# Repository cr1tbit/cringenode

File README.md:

# MOSNode

### A hackable IoT load switch prototyping platform

This device was probably the peak of my overengineeringness - I decided to create the most universal board for controlling low voltage outputs (Like LED stripes, motors, etc.).

In the end, it was too annoying to setup the matrix connections, so I just abandoned it.

## License

Copyright 2023 Jakub "cr1tbit" Sadowski.

* **Hardware** (KiCad sources, production files and this documentation) is
  licensed under the [CERN-OHL-P v2](LICENSE) (permissive). You may
  redistribute and modify it and make products using it under the terms of
  that licence.
* **Firmware** in [MOSNode-fw/](outduino-fw/) is licensed under the
  [MIT License](outduino-fw/LICENSE).

This source is distributed WITHOUT ANY EXPRESS OR IMPLIED WARRANTY, INCLUDING
OF MERCHANTABILITY, SATISFACTORY QUALITY AND FITNESS FOR A PARTICULAR PURPOSE.
Please see the CERN-OHL-P v2 for applicable conditions.

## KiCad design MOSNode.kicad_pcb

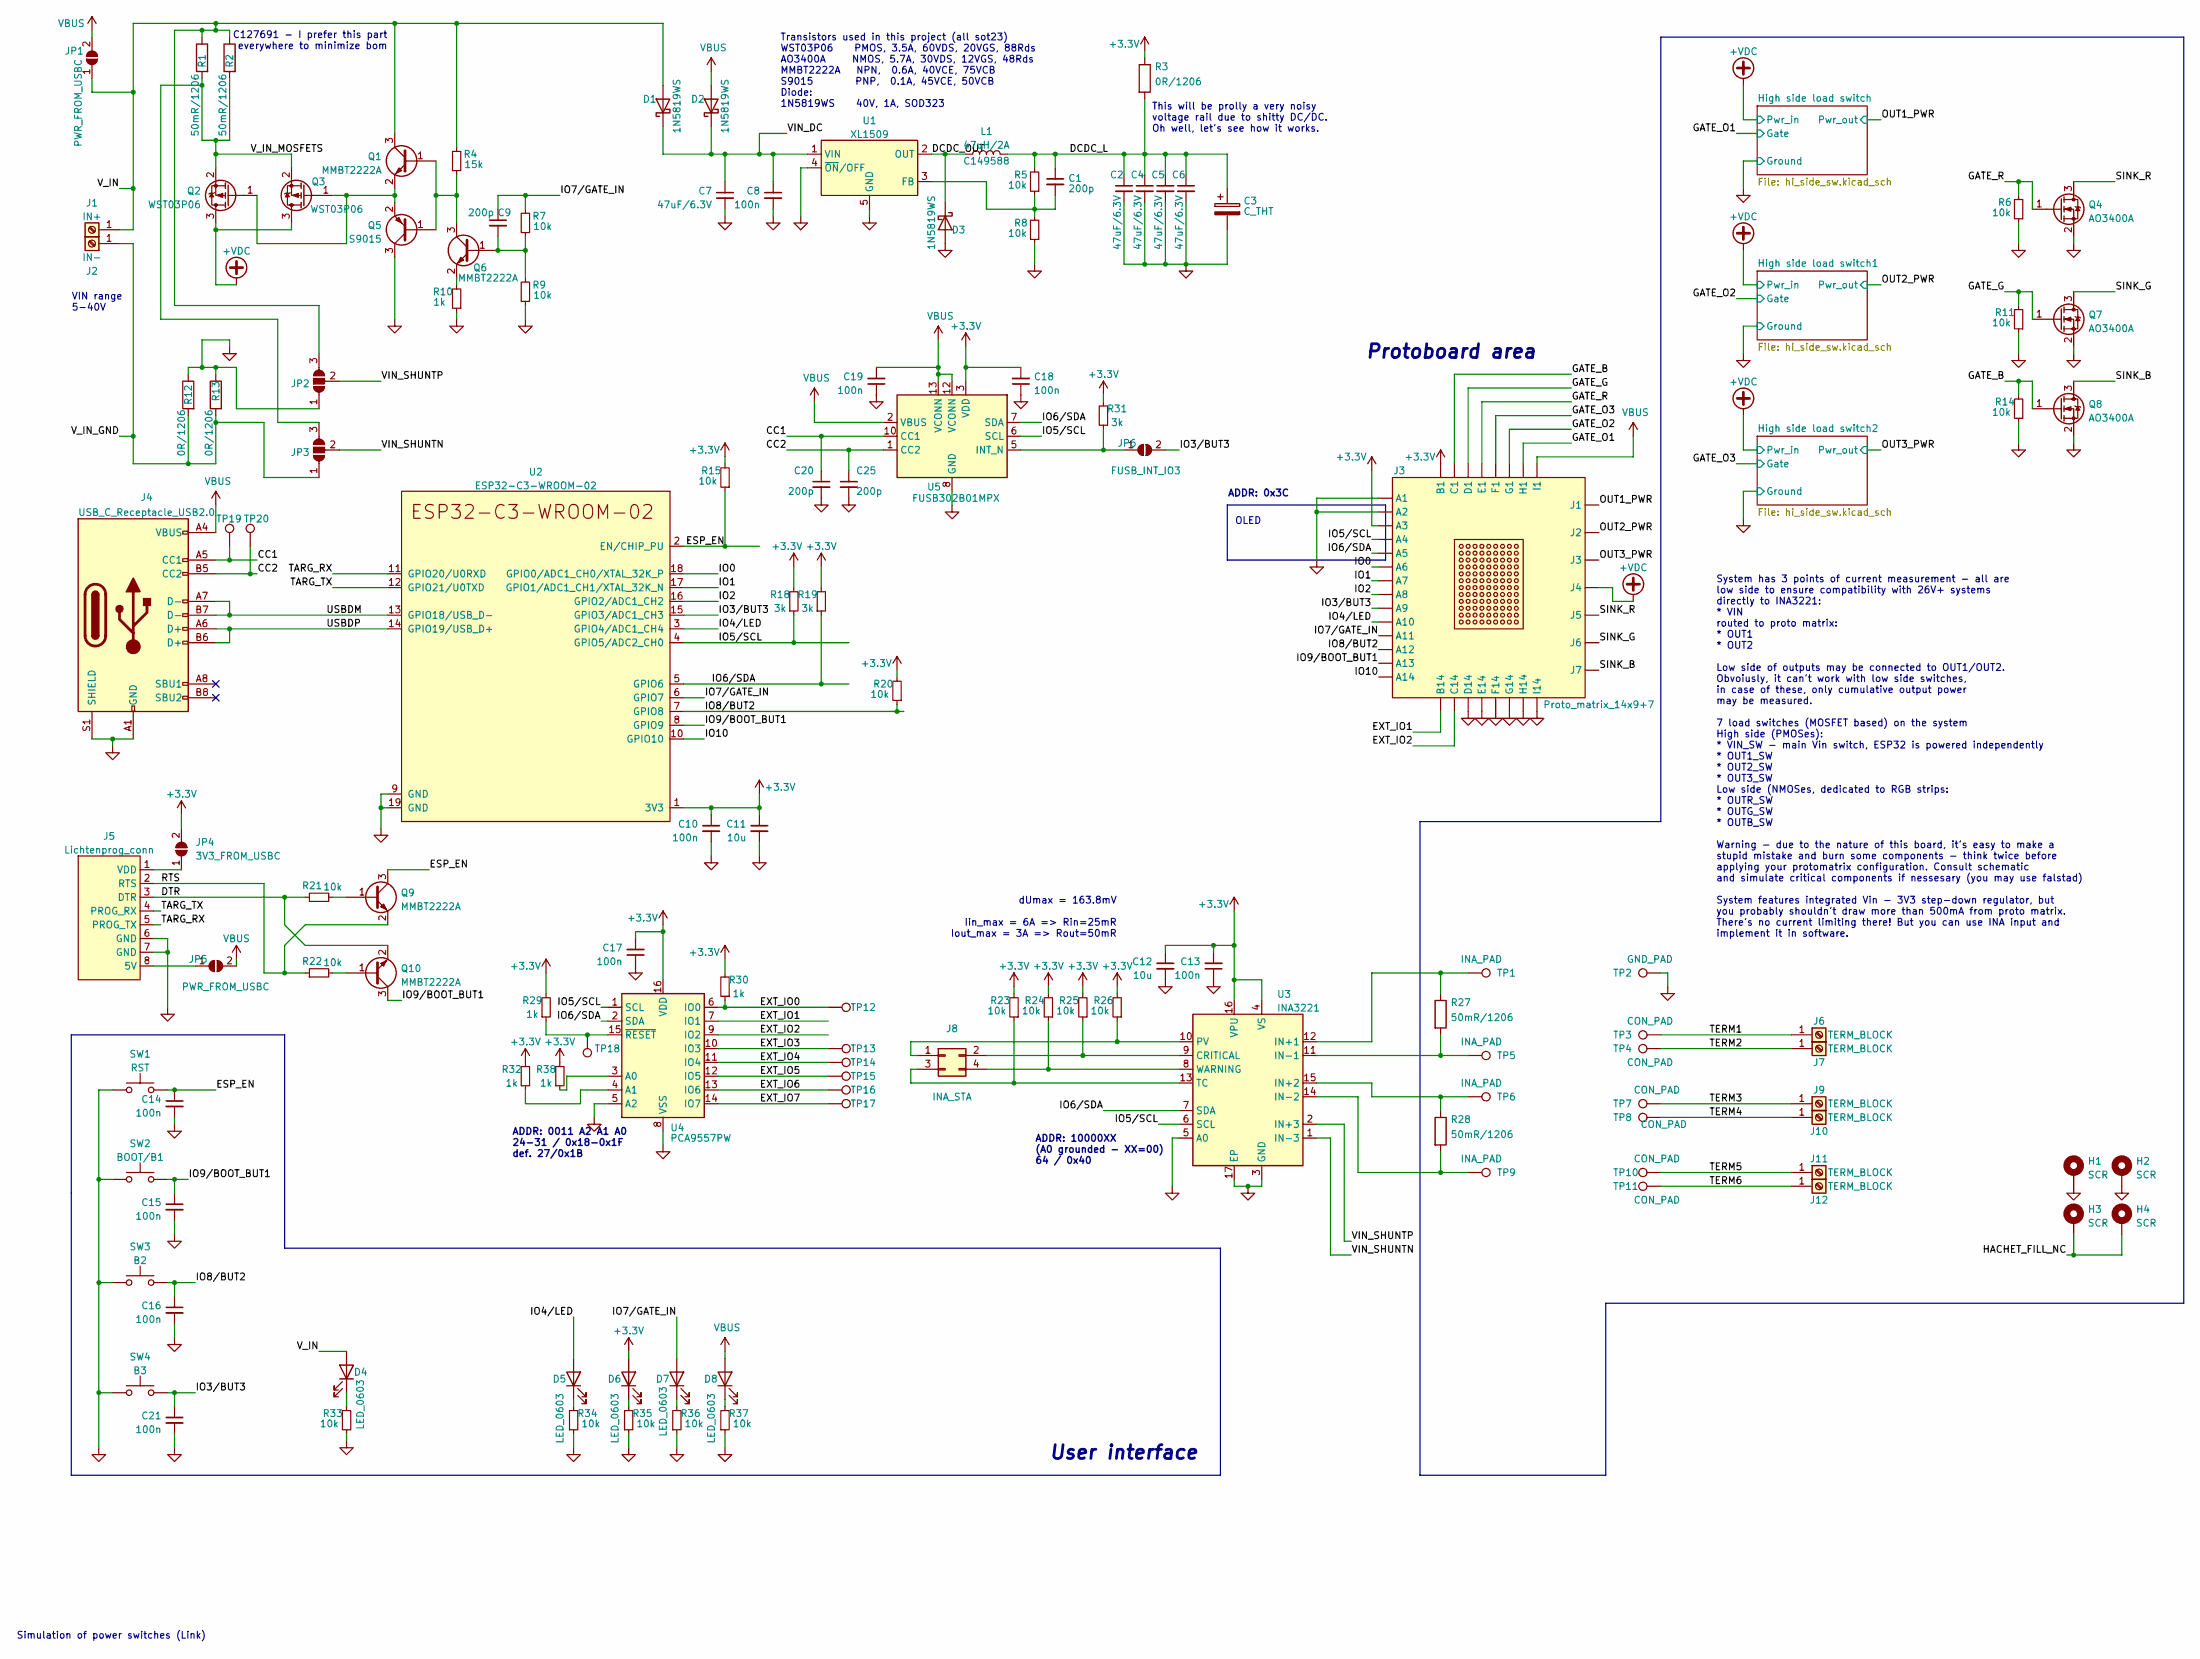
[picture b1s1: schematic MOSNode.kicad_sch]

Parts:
C1, C9, C20, C25: 200p; C_0402_1005Metric; LCSC C1530
C2, C4, C5, C6, C7: 47uF/6.3V; C_1206_3216Metric; LCSC C96123
C3: C_THT; CP_Radial_D10.0mm_P7.50mm; LCSC DNP
C8, C10, C13, C14, C15, C16, C17, C18, C19, C21: 100n; C_0402_1005Metric; LCSC C307331
C11, C12: 10u; C_0402_1005Metric; LCSC C15525
D1, D2, D3: 1N5819WS; D_SOD-323; LCSC C191023
D4, D5, D6, D7, D8: LED_0603; LED_0603_1608Metric_Pad1.05x0.95mm_HandSolder; LCSC C2290
H1, H2, H3, H4: SCR; MountingHole_3.2mm_M3_Pad_TopOnly; LCSC DNP
J1: IN+; DG235-5.0; LCSC DNP
J2: IN-; DG235-5.0; LCSC DNP
J3: Proto_matrix_14x9+7; LCSC DNP
J4: USB_C_Receptacle_USB2.0; USB_C_Receptacle_HRO_TYPE-C-31-M-12; LCSC C165948
J5: Lichtenprog_conn; Lichtenprog; LCSC DNP
J6, J7, J9, J10, J11, J12: TERM_BLOCK; DG235-5.0; LCSC DNP
J8: INA_STA; PinHeader_2x02_P2.54mm_Vertical; LCSC DNP
JP1, JP5: PWR_FROM_USBC; SolderJumper-2_P1.3mm_Open_TrianglePad1.0x1.5mm; LCSC DNP
JP2, JP3: SolderJumper_3_Open; SolderJumper-3_P2.0mm_Open_TrianglePad1.0x1.5mm_NumberLabels; LCSC DNP
JP4: 3V3_FROM_USBC; SolderJumper-2_P1.3mm_Open_TrianglePad1.0x1.5mm; LCSC DNP
JP6: FUSB_INT_IO3; SolderJumper-2_P1.3mm_Open_TrianglePad1.0x1.5mm; LCSC DNP
L1: 47uH/2A; L_Abracon_ASPI-0630LR; JLC C149588
Q1, Q6, Q9, Q10: MMBT2222A; SOT-23; LCSC C8512
Q2, Q3: WST03P06; SOT-23; LCSC C105166
Q4, Q7, Q8: AO3400A; SOT-23; LCSC C20917
Q5: S9015; SOT-23; LCSC C2149
R1, R2, R27, R28: 50mR/1206; R_1206_3216Metric_Pad1.30x1.75mm_HandSolder; LCSC C601102
R3, R12, R13: 0R/1206; R_1206_3216Metric_Pad1.30x1.75mm_HandSolder; LCSC C17888
R4: 15k; R_0402_1005Metric; LCSC C25756
R5, R6, R7, R8, R9, R11, R14, R15, R20, R21, R22, R23, R24, R25, R26, R33, R34, R35, R36, R37: 10k; R_0402_1005Metric; LCSC C25744
R10, R29, R30, R32, R38: 1k; R_0402_1005Metric; LCSC C11702
R18, R19, R31: 3k; R_0402_1005Metric; LCSC C25890
SW1: RST; SW_SPST_FSMSM; LCSC DNP
SW2: BOOT/B1; SW_SPST_FSMSM; LCSC DNP
SW3: B2; SW_SPST_FSMSM; LCSC DNP
SW4: B3; SW_SPST_FSMSM; LCSC DNP
TP1, TP5, TP6, TP9: INA_PAD; TestPoint_Pad_D2.5mm; LCSC DNP
TP2: GND_PAD; TestPoint_Pad_D2.5mm; LCSC DNP
TP3, TP4, TP7, TP8, TP10, TP11: CON_PAD; MountingHole_2.7mm_M2.5_DIN965_Pad; LCSC DNP
TP12, TP13, TP14, TP15, TP16, TP17, TP18, TP19, TP20: IOPAD; TestPoint_Pad_D1.0mm; LCSC DNP
U1: XL1509; SOIC-8_3.9x4.9mm_P1.27mm; LCSC C74192
U2: ESP32-C3-WROOM-02; LCSC DNP
U3: INA3221; Texas_RGV_S-PVQFN-N16_EP2.1x2.1mm; LCSC DNP
U4: PCA9557PW; TSSOP-16_4.4x5mm_P0.65mm; LCSC C141380
U5: FUSB302B01MPX; WQFN-14-1EP_2.5x2.5mm_P0.5mm_EP1.45x1.45mm; LCSC C132291

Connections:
+3.3V: C10.1, C11.1, C12.1, C13.2, C17.2, C18.2, D6.2 (A), J3.A3, J3.B1, JP4.2 (B), R3.1, R15.2, R18.2, R19.2, R20.2, R23.2, R24.2, R25.2, R26.2, R29.2, R30.2, R31.2, R32.2, R38.2, U2.1 (3V3), U3.4 (VS), U3.16 (VPU), U4.16 (VDD), U5.3 (VDD), U5.4 (VDD)
+VDC: J3.J4, Q2.3 (S), Q3.3 (S); also elsewhere on the board
/CC1: C20.1, J4.A5 (CC1), TP19.1, U5.10 (CC1), U5.11 (CC1)
/CC2: C25.1, J4.B5 (CC2), TP20.1, U5.1 (CC2), U5.14 (CC2)
/DCDC_L: C1.1, C2.1, C3.1, C4.1, C5.1, C6.1, L1.2, R3.2, R5.2
/DCDC_OUT: D3.1 (K), L1.1, U1.2 (OUT)
/DTR: J5.3 (DTR), Q10.2 (E), R21.1
/ESP_EN: C14.1, Q9.3 (C), R15.1, SW1.2, U2.2 (EN/CHIP_PU)
/EXT_IO0: R30.1, TP12.1, U4.6 (IO0)
/EXT_IO1: J3.B14, U4.7 (IO1)
/EXT_IO2: J3.C14, U4.9 (IO2)
/EXT_IO3: TP13.1, U4.10 (IO3)
/EXT_IO4: TP14.1, U4.11 (IO4)
/EXT_IO5: TP15.1, U4.12 (IO5)
/EXT_IO6: TP16.1, U4.13 (IO6)
/EXT_IO7: TP17.1, U4.14 (IO7)
/GATE_B: J3.C1, Q8.1 (G), R14.2
/GATE_G: J3.D1, Q7.1 (G), R11.2
/GATE_O1: J3.H1; also elsewhere on the board
/GATE_O2: J3.G1; also elsewhere on the board
/GATE_O3: J3.F1; also elsewhere on the board
/GATE_R: J3.E1, Q4.1 (G), R6.2
/HACHET_FILL_NC: H3.1, H4.1
/IO0: J3.A6, U2.18 (GPIO0/ADC1_CH0/XTAL_32K_P)
/IO1: J3.A7, U2.17 (GPIO1/ADC1_CH1/XTAL_32K_N)
/IO2: J3.A8, U2.16 (GPIO2/ADC1_CH2)
/IO3/BUT3: C21.1, J3.A9, JP6.2 (B), SW4.2, U2.15 (GPIO3/ADC1_CH3)
/IO4/LED: D5.2 (A), J3.A10, U2.3 (GPIO4/ADC1_CH4)
/IO5/SCL: J3.A4, R18.1, U2.4 (GPIO5/ADC2_CH0), U3.6 (SCL), U4.1 (SCL), U5.6 (SCL)
/IO6/SDA: J3.A5, R19.1, U2.5 (GPIO6), U3.7 (SDA), U4.2 (SDA), U5.7 (SDA)
/IO7/GATE_IN: C9.1, D7.2 (A), J3.A11, R7.2, U2.6 (GPIO7)
/IO8/BUT2: C16.1, J3.A12, R20.1, SW3.2, U2.7 (GPIO8)
/IO9/BOOT_BUT1: C15.1, J3.A13, Q10.3 (C), SW2.2, U2.8 (GPIO9)
/IO10: J3.A14, U2.10 (GPIO10)
/OUT1_PWR: J3.J1; also elsewhere on the board
/OUT2_PWR: J3.J2; also elsewhere on the board
/OUT3_PWR: J3.J3; also elsewhere on the board
/RTS: J5.2 (RTS), Q9.2 (E), R22.1
/SINK_B: J3.J7, Q8.3 (D)
/SINK_G: J3.J6, Q7.3 (D)
/SINK_R: J3.J5, Q4.3 (D)
/TARG_RX: J5.5 (PROG_TX), U2.11 (GPIO20/U0RXD)
/TARG_TX: J5.4 (PROG_RX), U2.12 (GPIO21/U0TXD)
/TERM1: J6.1, TP3.1
/TERM2: J7.1, TP4.1
/TERM3: J9.1, TP7.1
/TERM4: J10.1, TP8.1
/TERM5: J11.1, TP10.1
/TERM6: J12.1, TP11.1
/USBDM: J4.A7 (D-), J4.B7 (D-), U2.13 (GPIO18/USB_D-)
/USBDP: J4.A6 (D+), J4.B6 (D+), U2.14 (GPIO19/USB_D+)
/VIN_DC: C7.1, C8.1, D1.1 (K), D2.1 (K), U1.1 (VIN)
/VIN_SHUNTN: JP3.2 (C), U3.1 (IN-3)
/VIN_SHUNTP: JP2.2 (C), U3.2 (IN+3)
/V_IN: D1.2 (A), D4.2 (A), J1.1, JP1.1 (A), JP2.3 (B), Q1.3 (C), R1.1, R2.1, R4.2
/V_IN_GND: J2.1, JP3.1 (A), R12.2, R13.2
/V_IN_MOSFETS: JP3.3 (B), Q2.2 (D), Q3.2 (D), R1.2, R2.2
GND: C2.2, C3.2, C4.2, C5.2, C6.2, C7.2, C8.2, C10.2, C11.2, C12.2, C13.1, C14.2, C15.2, C16.2, C17.1, C18.1, C19.1, C20.2, C21.2, C25.2, D3.2 (A), H1.1, H2.1, J3.A1, J3.A2, J3.D14, J3.E14, J3.F14, J3.G14, J3.H14, J3.I14, J4.A1 (GND), J4.A12 (GND), J4.B1 (GND), J4.B12 (GND), J4.S1 (SHIELD), J5.6 (GND), J5.7 (GND), JP2.1 (A), Q4.2 (S), Q5.3 (C), Q7.2 (S), Q8.2 (S), R6.1, R8.1, R9.1, R10.1, R11.1, R12.1, R13.1, R14.1, R33.1, R34.1, R35.1, R36.1, R37.1, SW1.1, SW2.1, SW3.1, SW4.1, TP2.1, U1.4 (~ON/OFF), U1.5 (GND), U1.6 (GND), U1.7 (GND), U1.8 (GND), U2.9 (GND), U2.19 (GND), U3.3 (GND), U3.5 (A0), U3.17 (EP), U4.5 (A2), U4.8 (VSS), U5.8 (GND), U5.9 (GND), U5.15 (GND); also elsewhere on the board
unnamed: D4.1 (K), R33.2
unnamed: D5.1 (K), R34.2
unnamed: D6.1 (K), R35.2
unnamed: D7.1 (K), R36.2
unnamed: D8.1 (K), R37.2
unnamed: J5.8 (5V), JP5.1 (A)
unnamed: J5.1 (VDD), JP4.1 (A)
unnamed: J8.1, R26.1, U3.10 (PV)
unnamed: J8.2, R25.1, U3.9 (CRITICAL)
unnamed: J8.3, R23.1, U3.13 (TC)
unnamed: J8.4, R24.1, U3.8 (WARNING)
unnamed: JP6.1 (A), R31.1, U5.5 (INT_N)
unnamed: Q1.1 (B), Q5.1 (B), Q6.3 (C), R4.1
unnamed: Q1.2 (E), Q2.1 (G), Q3.1 (G), Q5.2 (E)
unnamed: C9.2, Q6.1 (B), R7.1, R9.2
unnamed: Q6.2 (E), R10.2
unnamed: Q9.1 (B), R21.2
unnamed: Q10.1 (B), R22.2
unnamed: C1.2, R5.1, R8.2, U1.3 (FB)
unnamed: R27.1, TP1.1, U3.12 (IN+1)
unnamed: R28.1, TP6.1, U3.15 (IN+2)
unnamed: R27.2, TP5.1, U3.11 (IN-1)
unnamed: R28.2, TP9.1, U3.14 (IN-2)
unnamed: R38.1, U4.3 (A0)
unnamed: R32.1, U4.4 (A1)
unnamed: R29.1, TP18.1, U4.15 (~RESET)
VBUS: C19.2, D2.2 (A), D8.2 (A), J3.I1, J4.A4 (VBUS), J4.A9 (VBUS), J4.B4 (VBUS), J4.B9 (VBUS), JP1.2 (B), JP5.2 (B), U5.2 (VBUS), U5.12 (VCONN), U5.13 (VCONN)

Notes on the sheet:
ADDR: 0011 A2 A1 A0 24-31 / 0x18-0x1F def. 27/0x1B
Transistors used in this project (all sot23) WST03P06 PMOS, 3.5A, 60VDS, 20VGS, 88Rds AO3400A NMOS, 5.7A, 30VDS, 12VGS, 48Rds MMBT2222A NPN, 0.6A, 40VCE, 75VCB S9015 PNP, 0.1A, 45VCE, 50VCB Diode: 1N5819WS 40V, 1A, SOD323
Protoboard area
ADDR: 10000XX (A0 grounded - XX=00) 64 / 0x40
System has 3 points of current measurement - all are low side to ensure compatibility with 26V+ systems directly to INA3221: * VIN routed to proto matrix: * OUT1 * OUT2 Low side of outputs may be connected to OUT1/OUT2. Obvoiusly, it can't work with low side switches, in case of these, only cumulat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
VIN range 5-40V
This will be prolly a very noisy voltage rail due to shitty DC/DC. Oh well, let's see how it works.
OLED
ADDR: 0x3C
User interface
C127691 - I prefer this part everywhere to minimize bom
Simulation of power switches (Link)
dUmax = 163.8mV Iin_max = 6A => Rin=25mR Iout_max = 3A => Rout=50mR

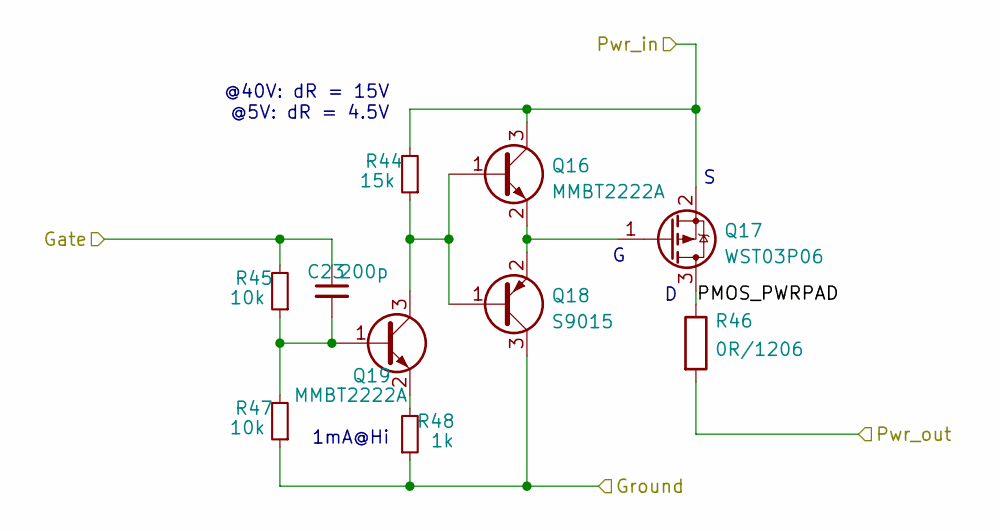
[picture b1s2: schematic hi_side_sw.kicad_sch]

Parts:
C23: 200p; C_0402_1005Metric; LCSC C1530
Q16, Q19: MMBT2222A; SOT-23; LCSC C8512
Q17: WST03P06; SOT-23; LCSC C105166
Q18: S9015; SOT-23; LCSC C2149
R44: 15k; R_0402_1005Metric; LCSC C25756
R45, R47: 10k; R_0402_1005Metric; LCSC C25744
R46: 0R/1206; R_1206_3216Metric_Pad1.30x1.75mm_HandSolder; LCSC C17888
R48: 1k; R_0402_1005Metric; LCSC C11702

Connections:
+VDC: Q16.3 (C), Q17.2 (D), R44.2; also elsewhere on the board
/GATE_O1: C23.1, R45.2; also elsewhere on the board
/High side load switch/PMOS_PWRPAD: Q17.3 (S), R46.1
/OUT1_PWR: R46.2; also elsewhere on the board
GND: Q18.3 (C), R47.1, R48.1; also elsewhere on the board
unnamed: Q16.1 (B), Q18.1 (B), Q19.3 (C), R44.1
unnamed: Q16.2 (E), Q17.1 (G), Q18.2 (E)
unnamed: C23.2, Q19.1 (B), R45.1, R47.2
unnamed: Q19.2 (E), R48.2

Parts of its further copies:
C22, C24: 200p; C_0402_1005Metric; LCSC C1530
Q12, Q15, Q20, Q23: MMBT2222A; SOT-23; LCSC C8512
Q13, Q21: WST03P06; SOT-23; LCSC C105166
Q14, Q22: S9015; SOT-23; LCSC C2149
R39, R49: 15k; R_0402_1005Metric; LCSC C25756
R40, R42, R50, R52: 10k; R_0402_1005Metric; LCSC C25744
R41, R51: 0R/1206; R_1206_3216Metric_Pad1.30x1.75mm_HandSolder; LCSC C17888
R43, R53: 1k; R_0402_1005Metric; LCSC C11702

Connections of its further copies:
+VDC: Q12.3 (C), Q13.2 (D), Q20.3 (C), Q21.2 (D), R39.2, R49.2; also elsewhere on the board
/GATE_O2: C22.1, R40.2; also elsewhere on the board
/GATE_O3: C24.1, R50.2; also elsewhere on the board
/High side load switch1/PMOS_PWRPAD: Q13.3 (S), R41.1
/High side load switch2/PMOS_PWRPAD: Q21.3 (S), R51.1
/OUT2_PWR: R41.2; also elsewhere on the board
/OUT3_PWR: R51.2; also elsewhere on the board
GND: Q14.3 (C), Q22.3 (C), R42.1, R43.1, R52.1, R53.1; also elsewhere on the board
unnamed: Q12.1 (B), Q14.1 (B), Q15.3 (C), R39.1
unnamed: Q12.2 (E), Q13.1 (G), Q14.2 (E)
unnamed: C22.2, Q15.1 (B), R40.1, R42.2
unnamed: Q15.2 (E), R43.2
unnamed: Q20.1 (B), Q22.1 (B), Q23.3 (C), R49.1
unnamed: Q20.2 (E), Q21.1 (G), Q22.2 (E)
unnamed: C24.2, Q23.1 (B), R50.1, R52.2
unnamed: Q23.2 (E), R53.2

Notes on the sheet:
1mA@Hi
@40V: dR = 15V @5V: dR = 4.5V

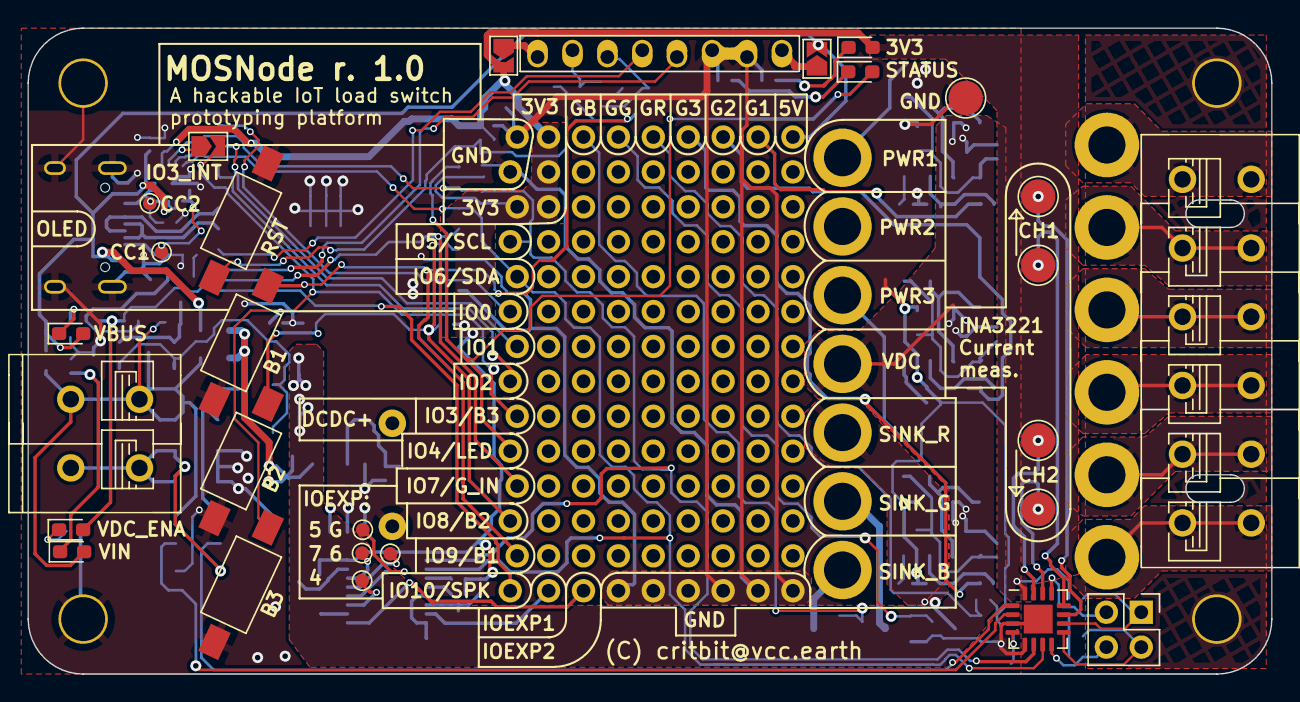
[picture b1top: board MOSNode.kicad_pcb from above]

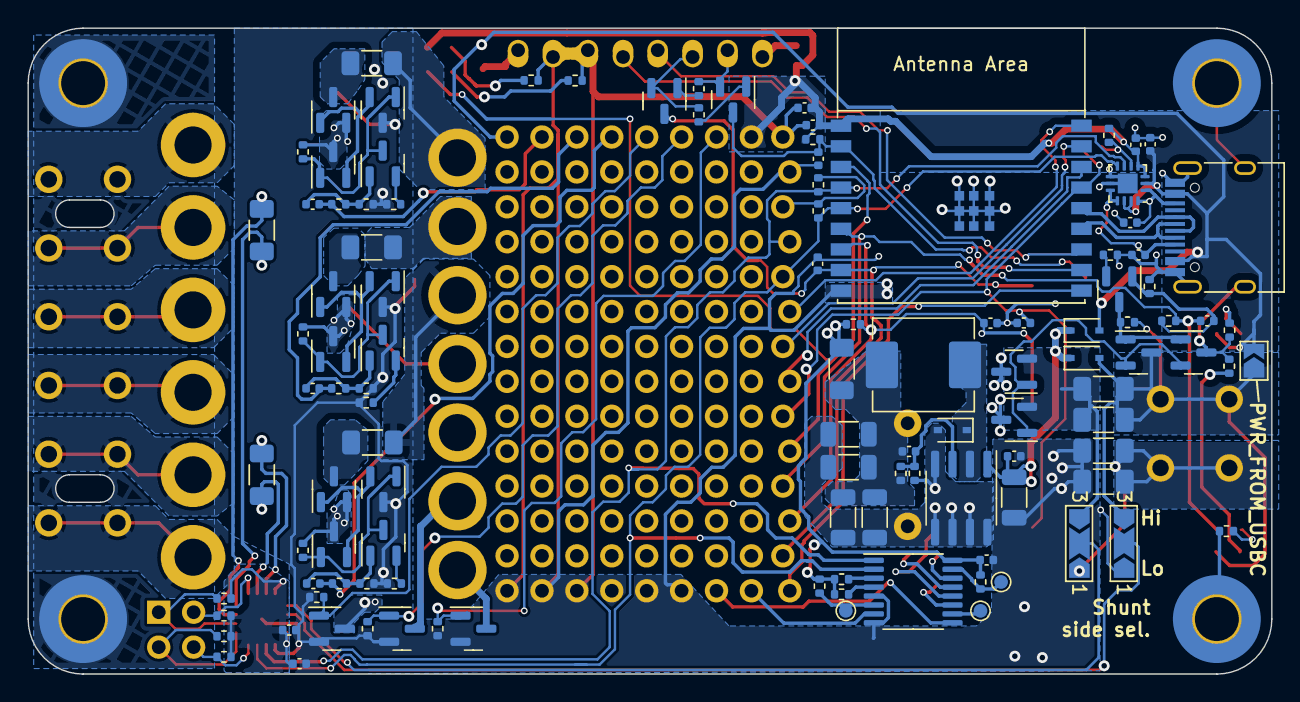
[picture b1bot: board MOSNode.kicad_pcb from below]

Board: 2 copper layers, 90.5 x 47.0 mm, 158 parts (116 on the bottom side), 100 nets.

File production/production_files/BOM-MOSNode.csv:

Comment,Designator,Footprint,LCSC
WST03P06,"Q13,Q17,Q2,Q21,Q3",SOT-23,C105166
1k,"R10,R29,R30,R32,R38,R43,R48,R53",R_0402_1005Metric,C11702
FUSB302B01MPX,U5,WQFN-14-1EP_2.5x2.5mm_P0.5mm_EP1.45x1.45mm,C132291
PCA9557PW,U4,TSSOP-16_4.4x5mm_P0.65mm,C141380
47uH/2A,L1,L_Abracon_ASPI-0630LR,C149588
200p,"C1,C20,C22,C23,C24,C25,C9",C_0402_1005Metric,C1530
10u,"C11,C12",C_0402_1005Metric,C15525
USB_C_Receptacle_USB2.0,J4,USB_C_Receptacle_HRO_TYPE-C-31-M-12,C165948
0R/1206,"R12,R13,R3,R41,R46,R51",R_1206_3216Metric_Pad1.30x1.75mm_HandSolder,C17888
1N5819WS,"D1,D2,D3",D_SOD-323,C191023
AO3400A,"Q4,Q7,Q8",SOT-23,C20917
S9015,"Q14,Q18,Q22,Q5",SOT-23,C2149
LED_0603,"D4,D5,D6,D7,D8",LED_0603_1608Metric_Pad1.05x0.95mm_HandSolder,C2290
10k,"R11,R14,R15,R20,R21,R22,R23,R24,R25,R26,R33,R34,R35,R36,R37,R40,R42,R45,R47,R5,R50,R52,R6,R7,R8,R9",R_0402_1005Metric,C25744
15k,"R39,R4,R44,R49",R_0402_1005Metric,C25756
3k,"R18,R19,R31",R_0402_1005Metric,C25890
100n,"C10,C13,C14,C15,C16,C17,C18,C19,C21,C8",C_0402_1005Metric,C307331
50mR/1206,"R1,R2,R27,R28",R_1206_3216Metric_Pad1.30x1.75mm_HandSolder,C601102
XL1509,U1,SOIC-8_3.9x4.9mm_P1.27mm,C74192
MMBT2222A,"Q1,Q10,Q12,Q15,Q16,Q19,Q20,Q23,Q6,Q9",SOT-23,C8512
47uF/6.3V,"C2,C4,C5,C6,C7",C_1206_3216Metric,C96123
IN+,J1,DG235-5.0,
FUSB_INT_IO3,JP6,SolderJumper-2_P1.3mm_Open_TrianglePad1.0x1.5mm,
INA_PAD,TP5,TestPoint_Pad_D2.5mm,
B3,SW4,SW_SPST_FSMSM,
TERM_BLOCK,J7,DG235-5.0,
CON_PAD,TP4,MountingHole_2.7mm_M2.5_DIN965_Pad,
INA_STA,J8,PinHeader_2x02_P2.54mm_Vertical,
CON_PAD,TP11,MountingHole_2.7mm_M2.5_DIN965_Pad,
INA_PAD,TP9,TestPoint_Pad_D2.5mm,
BOOT/B1,SW2,SW_SPST_FSMSM,
TERM_BLOCK,J10,DG235-5.0,
TERM_BLOCK,J6,DG235-5.0,
INA_PAD,TP1,TestPoint_Pad_D2.5mm,
IOPAD,TP20,TestPoint_Pad_D1.0mm,
IOPAD,TP14,TestPoint_Pad_D1.0mm,
IOPAD,TP16,TestPoint_Pad_D1.0mm,
GND_PAD,TP2,TestPoint_Pad_D2.5mm,
PWR_FROM_USBC,JP5,SolderJumper-2_P1.3mm_Open_TrianglePad1.0x1.5mm,
TERM_BLOCK,J12,DG235-5.0,
Proto_matrix_14x9+7,J3,Proto_matrix_14x9+7,
C_THT,C3,CP_Radial_D10.0mm_P7.50mm,
IOPAD,TP15,TestPoint_Pad_D1.0mm,
IN-,J2,DG235-5.0,
IOPAD,TP17,TestPoint_Pad_D1.0mm,
RST,SW1,SW_SPST_FSMSM,
INA3221,U3,Texas_RGV_S-PVQFN-N16_EP2.1x2.1mm,
B2,SW3,SW_SPST_FSMSM,
3V3_FROM_USBC,JP4,SolderJumper-2_P1.3mm_Open_TrianglePad1.0x1.5mm,
INA_PAD,TP6,TestPoint_Pad_D2.5mm,
TERM_BLOCK,J11,DG235-5.0,
CON_PAD,TP8,MountingHole_2.7mm_M2.5_DIN965_Pad,
CON_PAD,TP3,MountingHole_2.7mm_M2.5_DIN965_Pad,
Lichtenprog_conn,J5,Lichtenprog,
IOPAD,TP19,TestPoint_Pad_D1.0mm,
CON_PAD,TP10,MountingHole_2.7mm_M2.5_DIN965_Pad,
TERM_BLOCK,J9,DG235-5.0,
CON_PAD,TP7,MountingHole_2.7mm_M2.5_DIN965_Pad,
ESP32-C3-WROOM-02,U2,ESP32-C3-WROOM-02,
IOPAD,TP12,TestPoint_Pad_D1.0mm,
SCR,H4,MountingHole_3.2mm_M3_Pad_TopOnly,
SolderJumper_3_Open,JP2,SolderJumper-3_P2.0mm_Open_TrianglePad1.0x1.5mm_NumberLabels,
SCR,H1,MountingHole_3.2mm_M3_Pad_TopOnly,
IOPAD,TP13,TestPoint_Pad_D1.0mm,
PWR_FROM_USBC,JP1,SolderJumper-2_P1.3mm_Open_TrianglePad1.0x1.5mm,
IOPAD,TP18,TestPoint_Pad_D1.0mm,
SCR,H3,MountingHole_3.2mm_M3_Pad_TopOnly,
SCR,H2,MountingHole_3.2mm_M3_Pad_TopOnly,
SolderJumper_3_Open,JP3,SolderJumper-3_P2.0mm_Open_TrianglePad1.0x1.5mm_NumberLabels,

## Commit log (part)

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2022-10-12 initing stuff
2022-10-23 work rly hard on schematic
2022-10-24 mostly finishing schematic
2022-10-29 pivoting to protoboard-matrix
2022-11-12 finish this unholy abomination
2023-07-09 replace audio with IOexp + PD controller, project rename
2023-07-22 production
2023-08-29 the boilerplate for fw
2023-08-31 finished template project
2023-09-17 add ina stub
2023-09-17 wrap current handling in class
